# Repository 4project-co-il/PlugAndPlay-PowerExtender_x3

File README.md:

# PlugAndPlay: Power Extender x3
This is the repository with the files for PlugAndPlay power externder board.

The board has 4x PnP power module ports and allows connection of 4x PnP power modules.
All the ports are connected in parallel. One port will be used as an input and 3x ports as extended outputs.

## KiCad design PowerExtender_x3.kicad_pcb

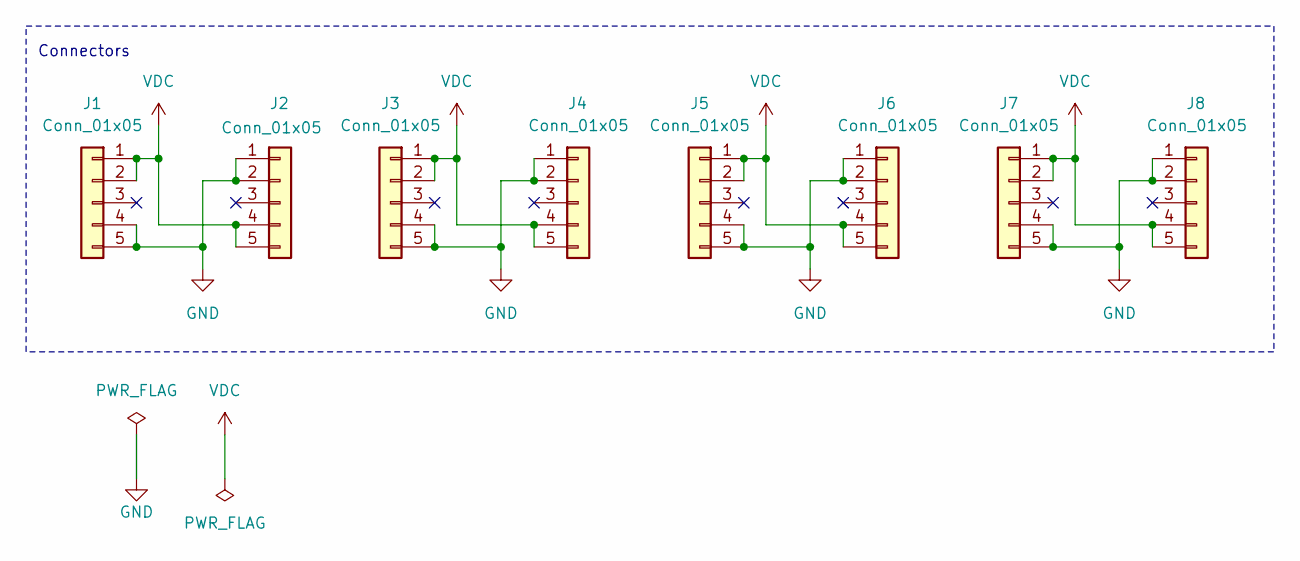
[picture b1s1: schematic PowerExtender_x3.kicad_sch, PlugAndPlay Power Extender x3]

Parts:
J1, J3, J5, J7: Conn_01x05; PinSocket_1x05_P2.54mm_Vertical_SMD_Pin1Right; MPN RealRun
J2, J4, J6, J8: Conn_01x05; PinSocket_1x05_P2.54mm_Vertical_SMD_Pin1Left; MPN RealRun

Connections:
GND: J1.4, J1.5, J2.1, J2.2, J3.4, J3.5, J4.1, J4.2, J5.4, J5.5, J6.1, J6.2, J7.4, J7.5, J8.1, J8.2
VDC: J1.1, J1.2, J2.4, J2.5, J3.1, J3.2, J4.4, J4.5, J5.1, J5.2, J6.4, J6.5, J7.1, J7.2, J8.4, J8.5

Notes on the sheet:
Connectors

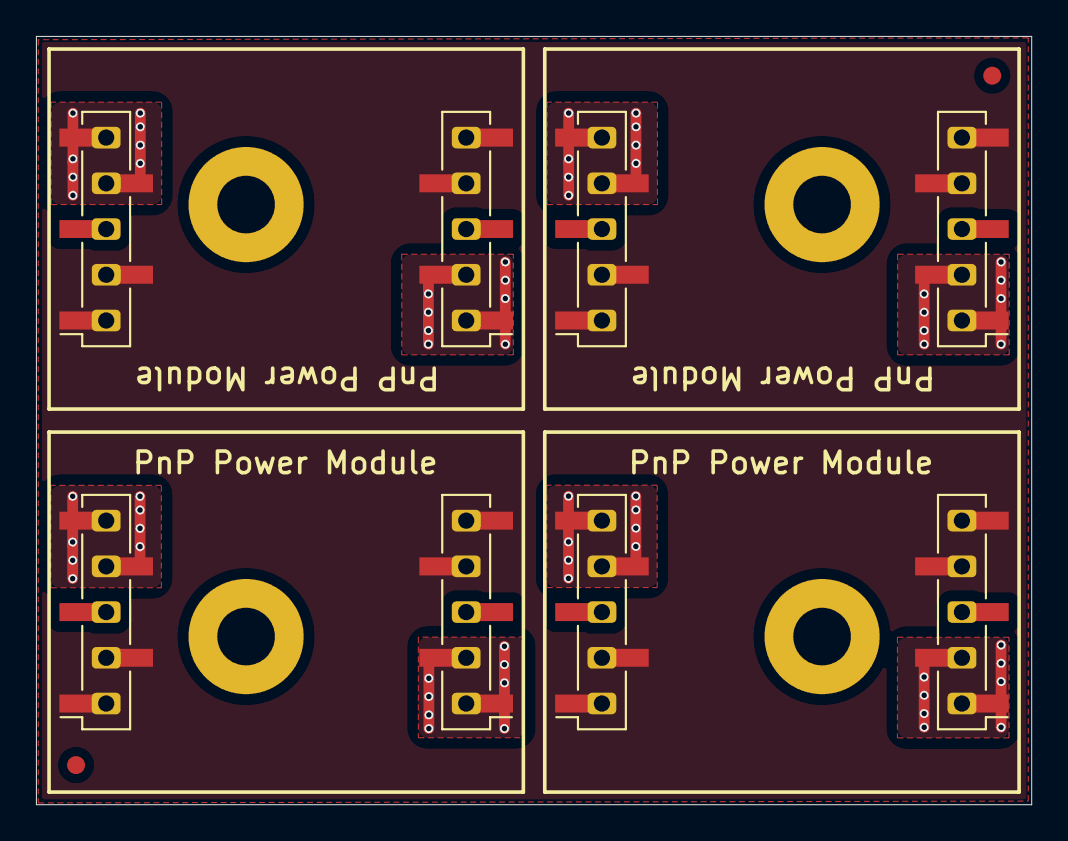
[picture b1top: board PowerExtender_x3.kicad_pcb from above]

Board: 2 copper layers, 55.3 x 42.7 mm, 8 parts (0 on the bottom side), 2 nets.

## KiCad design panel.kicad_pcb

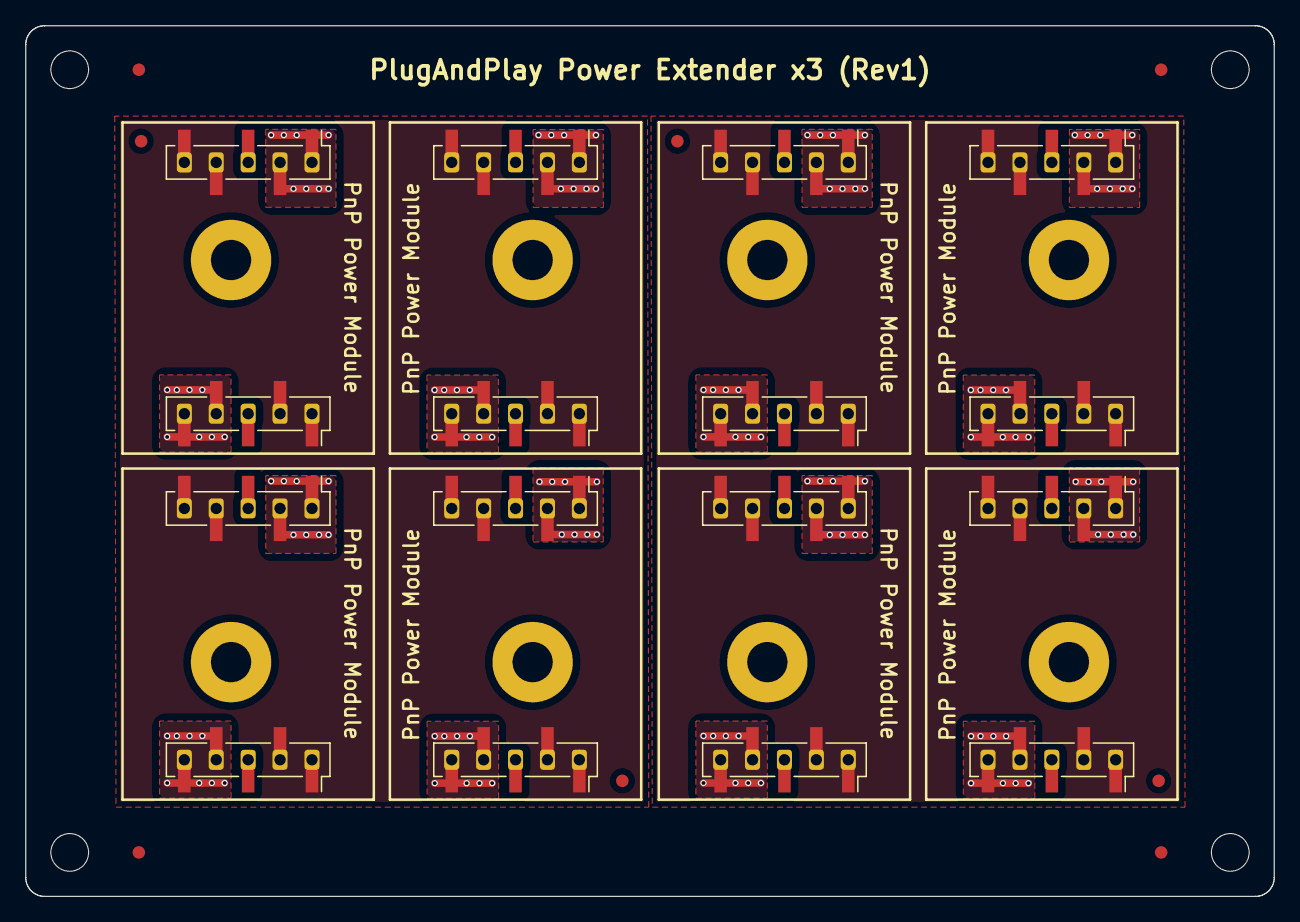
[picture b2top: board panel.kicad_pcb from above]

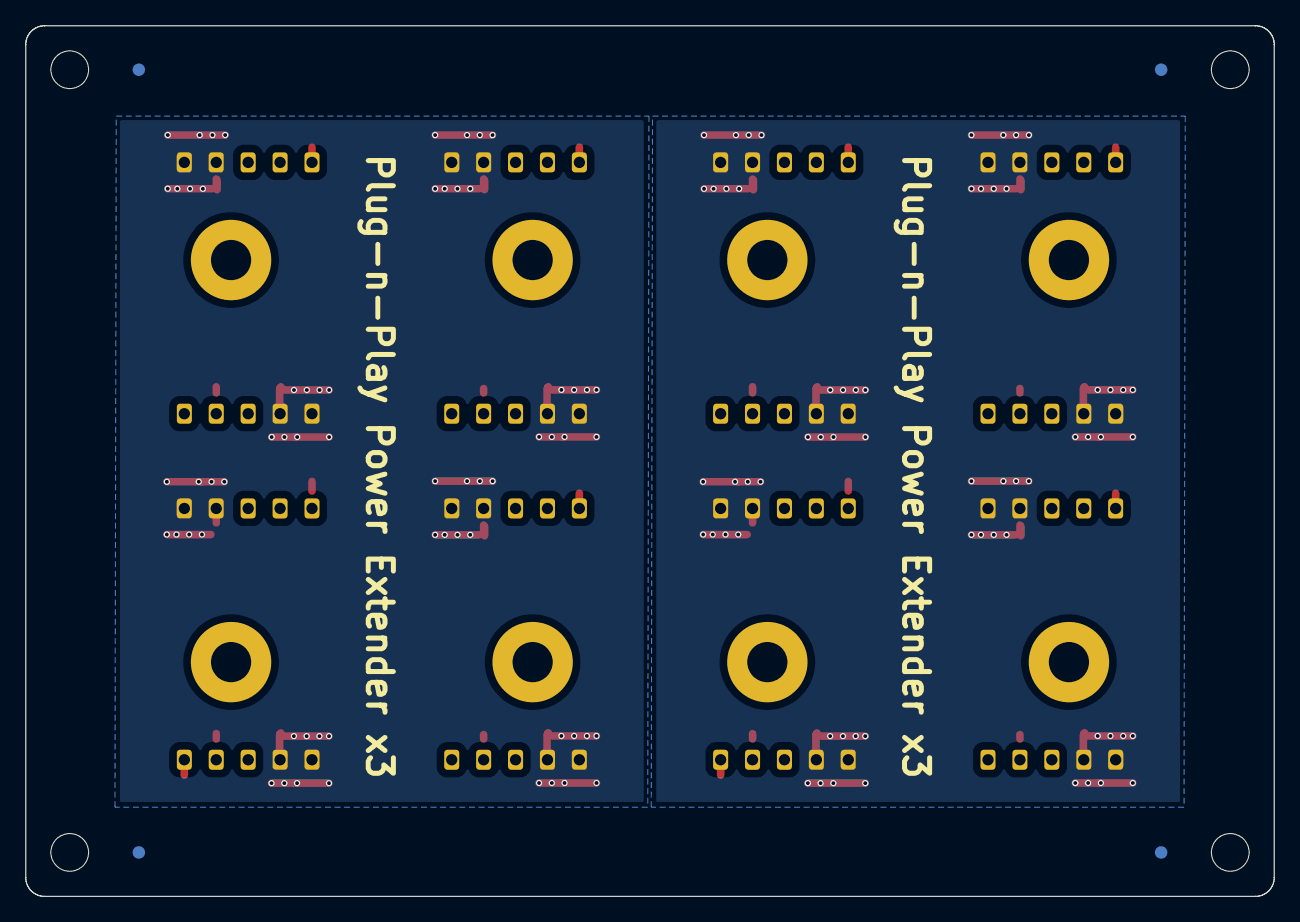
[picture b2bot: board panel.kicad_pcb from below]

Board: 2 copper layers, 99.4 x 69.3 mm, 28 parts (4 on the bottom side), 4 nets.

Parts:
J1, J1#2, J3, J3#2, J5, J5#2, J7, J7#2: Conn_01x05; PinSocket_1x05_P2.54mm_Vertical_SMD_Pin1Right
J2, J2#2, J4, J4#2, J6, J6#2, J8, J8#2: Conn_01x05; PinSocket_1x05_P2.54mm_Vertical_SMD_Pin1Left
KiKit_FID_B_1, KiKit_FID_B_2, KiKit_FID_B_3, KiKit_FID_B_4: Fiducial
KiKit_FID_T_1, KiKit_FID_T_2, KiKit_FID_T_3, KiKit_FID_T_4: Fiducial
KiKit_TO_1, KiKit_TO_2, KiKit_TO_3, KiKit_TO_4: NPTH

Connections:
Board_0-GND: J1.4, J1.5, J2#2.1, J2#2.2, J3#2.4, J3#2.5, J4.1, J4.2, J5.4, J5.5, J6#2.1, J6#2.2, J7.4, J7.5, J8.1, J8.2
Board_0-VDC: J1.1, J1.2, J2#2.4, J2#2.5, J3#2.1, J3#2.2, J4.4, J4.5, J5.1, J5.2, J6#2.4, J6#2.5, J7.1, J7.2, J8.4, J8.5
Board_1-GND: J1#2.4, J1#2.5, J2.1, J2.2, J3.4, J3.5, J4#2.1, J4#2.2, J5#2.4, J5#2.5, J6.1, J6.2, J7#2.4, J7#2.5, J8#2.1, J8#2.2
Board_1-VDC: J1#2.1, J1#2.2, J2.4, J2.5, J3.1, J3.2, J4#2.4, J4#2.5, J5#2.1, J5#2.2, J6.4, J6.5, J7#2.1, J7#2.2, J8#2.4, J8#2.5
